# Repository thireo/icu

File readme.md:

# DTUE Irish Coffee Unlimited

## Requirements specification
* Vægtplade som koppen står på
  * Tom kop på plade, efterfulgt af kaffe påfyldning for vejning og estimering af ledig plads.
  * Kontrollerer også om ingredienser kommer i koppen og melder fejl efter tid. 
* Peristal pumpe til dosering whisky
* Aktuator til flødeskum
* Omrørings enhed, motor med decentreret ske
* Rørsnegl, til transport af brun farin. 
  * Sneglebor og rør med øget diameter.

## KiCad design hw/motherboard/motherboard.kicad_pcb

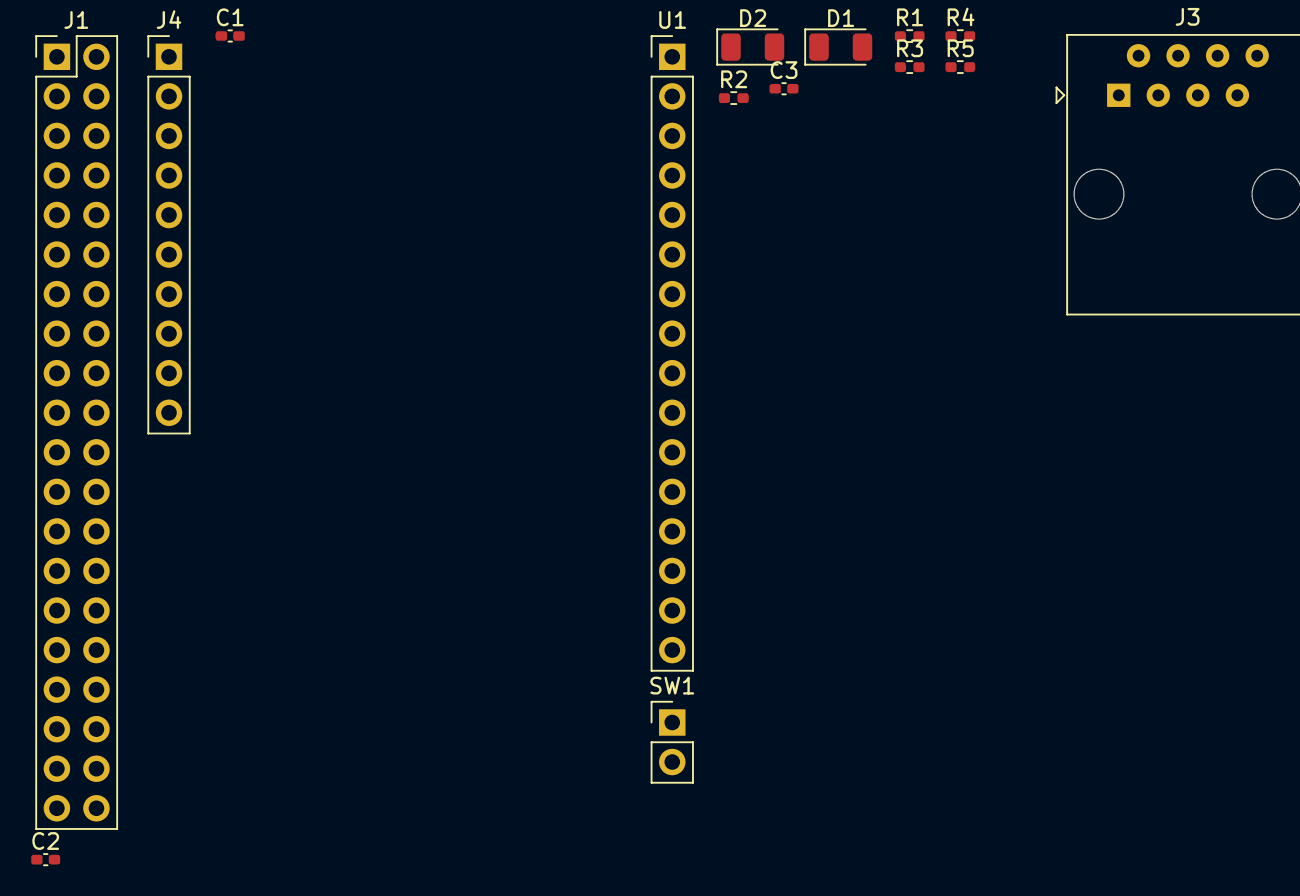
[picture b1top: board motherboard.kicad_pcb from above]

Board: 2 copper layers, 15 parts (0 on the bottom side), 30 nets, no tracks yet.

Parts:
C1: 10u; C_0402_1005Metric_Pad0.74x0.62mm_HandSolder
C2, C3: 100n; C_0402_1005Metric_Pad0.74x0.62mm_HandSolder
D1: PWR; D_1206_3216Metric
D2: STATUS; D_1206_3216Metric
J1: Raspberry_Pi_2_3; PinHeader_2x20_P2.54mm_Vertical
J3: RJ45; RJ45_Amphenol_54602-x08_Horizontal
J4: Conn_01x10; PinHeader_1x10_P2.54mm_Vertical
R1: 100k; R_0402_1005Metric_Pad0.72x0.64mm_HandSolder
R2, R3: 100; R_0402_1005Metric_Pad0.72x0.64mm_HandSolder
R4: 2k; R_0402_1005Metric_Pad0.72x0.64mm_HandSolder
R5: 220; R_0402_1005Metric_Pad0.72x0.64mm_HandSolder
SW1: SW_Push; PinHeader_1x02_P2.54mm_Vertical
U1: RC1602A; PinHeader_1x16_P2.54mm_Vertical

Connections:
+3V3: C1.1, C2.1, J1.1 (3V3), J1.17 (3V3), J3.6, J4.1, R1.1
+5V: J1.2 (5V), J1.4 (5V), R5.2, U1.2 (VDD)
/DC Motor Control/CS: J1.7 (GCLK0/GPIO4), J3.3
/DC Motor Control/SCL: J1.5 (SCL/GPIO3), J3.2
/DC Motor Control/SDA: J1.3 (SDA/GPIO2), J3.1
/DC Motor Control/STATUS: J1.23 (SCLK0/GPIO11), J3.4
/DC Motor Control/~RESET: J1.29 (GCLK1/GPIO5), J3.5
/User Interface/BUTTON: C3.1, J1.40 (GPIO21/SCLK1), R1.2, SW1.1
/User Interface/LCD_D4: J1.15 (GPIO22), U1.11 (DB4)
/User Interface/LCD_D5: J1.16 (GPIO23), U1.12 (DB5)
/User Interface/LCD_D6: J1.18 (GPIO24), U1.13 (DB6)
/User Interface/LCD_D7: J1.22 (GPIO25), U1.14 (DB7)
/User Interface/LCD_EN: J1.37 (GPIO26), U1.6 (E)
/User Interface/LCD_RS: J1.13 (GPIO27), U1.4 (RS)
/User Interface/LED_PWR: J1.32 (PWM0/GPIO12), R3.1
/User Interface/LED_STATUS: J1.33 (PWM1/GPIO13), R2.1
GND: C1.2, C2.2, C3.2, D1.1 (K), D2.1 (K), J1.6 (GND), J1.9 (GND), J1.14 (GND), J1.20 (GND), J1.25 (GND), J1.30 (GND), J1.34 (GND), J1.39 (GND), J3.7, J3.8, R4.2, SW1.2, U1.1 (VSS), U1.5 (R/W), U1.16 (K)
unnamed: D1.2 (A), R2.2
unnamed: D2.2 (A), R3.2
unnamed: J1.8 (GPIO14/TXD), J4.4
unnamed: J1.10 (GPIO15/RXD), J4.5
unnamed: J1.11 (GPIO17), J4.7
unnamed: J1.12 (GPIO18/PWM0), J4.8
unnamed: J1.27 (ID_SD/GPIO0), J4.3
unnamed: J1.28 (ID_SC/GPIO1), J4.2
unnamed: J1.35 (GPIO19/MISO1), J4.9
unnamed: J1.36 (GPIO16), J4.6
unnamed: J1.38 (GPIO20/MOSI1), J4.10
unnamed: R4.1, U1.3 (VO)
unnamed: R5.1, U1.15 (A/VEE)

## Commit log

2022-03-06 Added req. spec.
2022-03-06 Minor formatting on readme
2022-03-06 Renamed readme
2022-03-16 Initial HW commit
2022-03-16 Added LEDs and annotation.
2022-03-16 Added gitignore with Kicad6 backups ignored.
2022-03-16 Added user interface to schematics.
2022-03-16 Added not used header.
2022-03-16 Updated page settings in schematic
2022-03-17 Fixed DRC errors on schematic
2022-03-17 Fixed footprints for alle components
